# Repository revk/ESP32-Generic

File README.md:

# ESP32-Generic

Now at [Codeberg](https://codeberg.org/RevK/ESP32-Generic)

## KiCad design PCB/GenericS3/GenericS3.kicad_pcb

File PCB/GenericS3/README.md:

# GenericS3

## Trademark

This is an open source project, but bear in mind you cannot sell boards bearing the Andrews & Arnold Ltd name, the A&A logo, the registered trademark AJK logo, or the GS1 allocated EANs assigned to Andrews & Arnold Ltd.

## PCB Designs

These files are for use with [KiCAD](https://www.kicad.org).

- [GenericS3](GenericS3.kicad_pro)
## 3D

3D case designs are normally automatically created from the PCB so as to ensure correct details and placement of apertures, etc.

|Design|Bottom|Top|
|------|------|---|
|GenericS3|[GenericS3B](GenericS3B.stl)|[GenericS3T](GenericS3T.stl)|

## Images

---

*Auto generated README.md 2025-08-25T15:22:12*

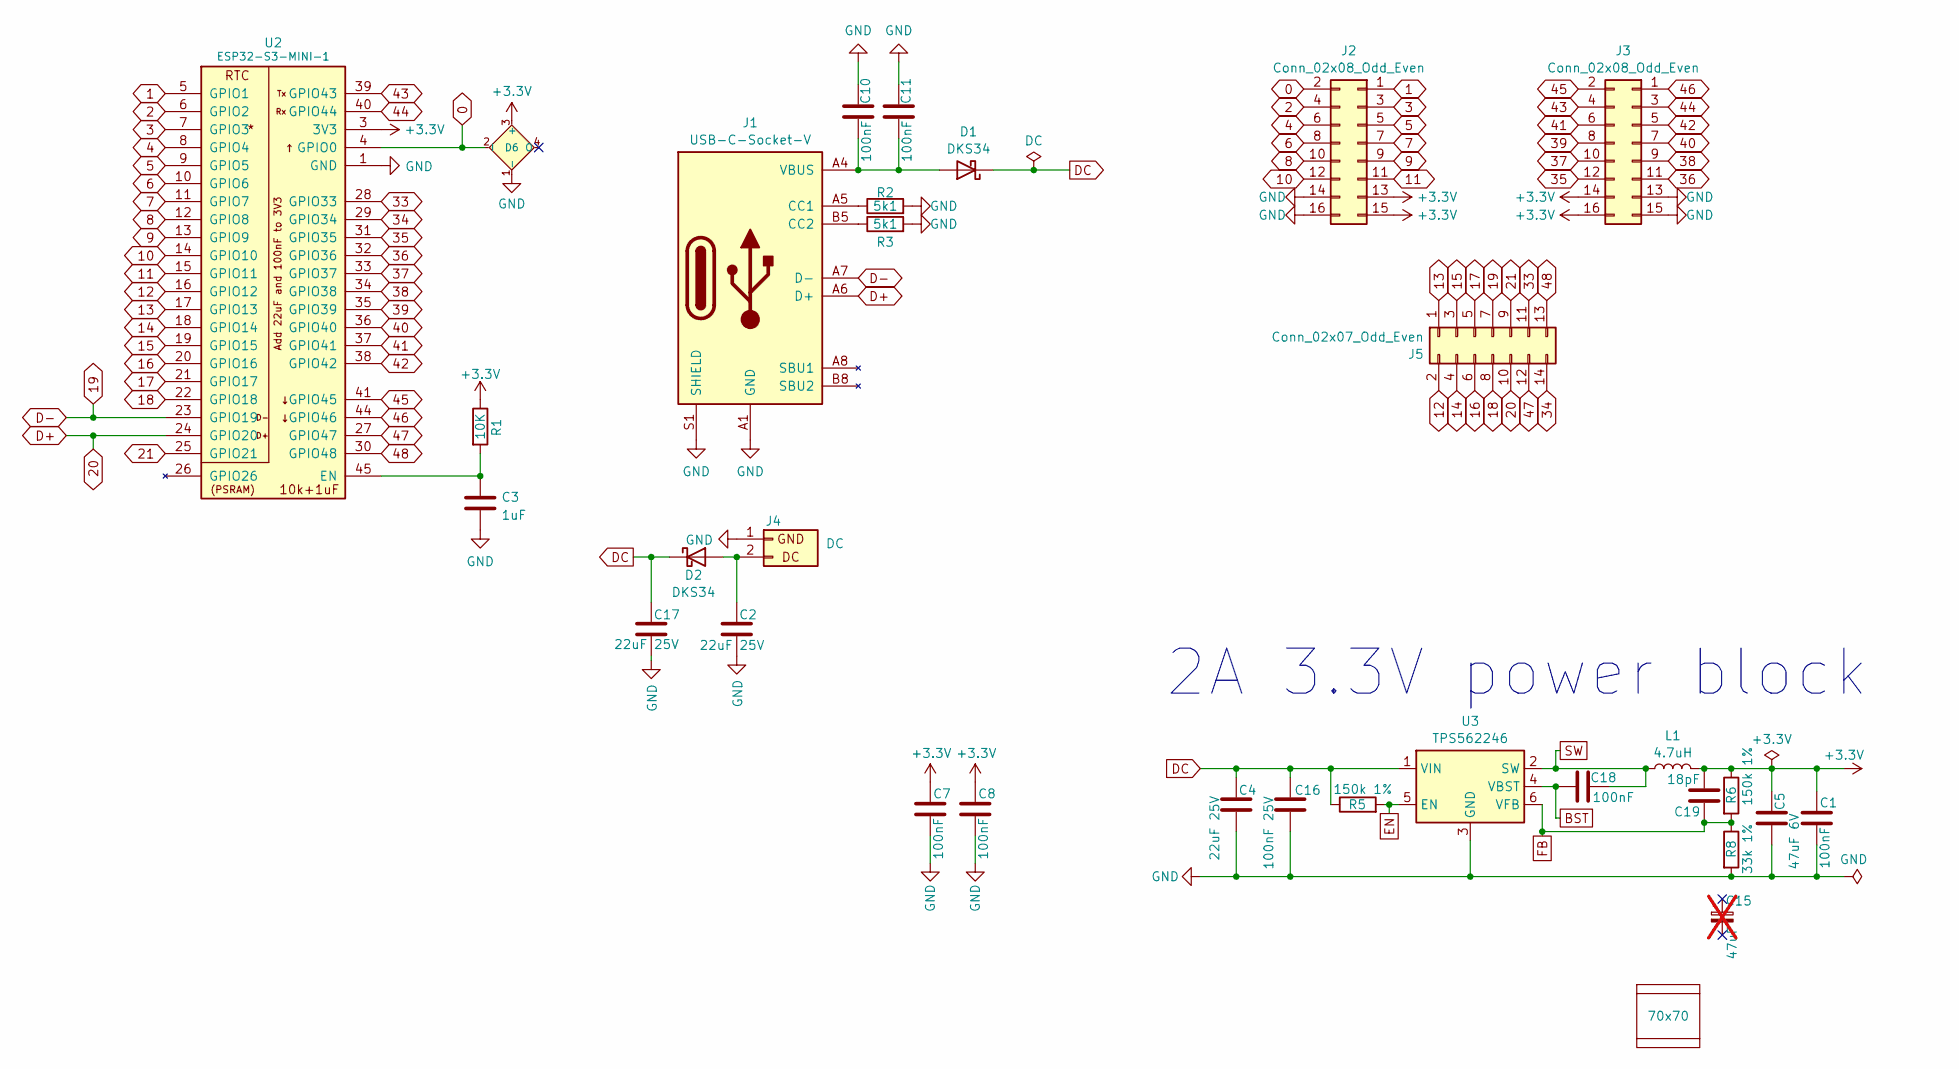
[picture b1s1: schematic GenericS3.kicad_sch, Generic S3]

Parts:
C1, C7, C8, C10, C11, C18: 100nF; C_0201; MPN C76934
C2, C4, C17: 22uF 25V; C_0805; MPN C45783
C3: 1uF; C_0201
C5: 47uF 6V; C_0805; MPN C16780
C15: 47uF; C_0805_Tant; MPN C1954938; not fitted
C16: 100nF 25V; C_0402; MPN C56392
C19: 18pF; C_0201; MPN C62164
D1, D2: DKS34; D_SOD-123FL; MPN C727076
D6: XL-1010RGBC-WS2812B; SMD1615; MPN C5349954
J1: USB-C-Socket-V; USB-C-Socket-H; MPN C709357
J2, J3: Conn_02x08_Odd_Even; PinHeader_2x08_P2.54mm_Vertical
J4: DC; WAGO-2060-452-998-404; MPN C2765055
J5: Conn_02x07_Odd_Even; PinHeader_2x07_P2.54mm_Vertical
L1: 4.7uH; L_5x5; MPN C307876
PCB1: 70x70; PCB7070
R1: 10K; R_0201; MPN C106225
R2, R3: 5k1; R_0201; MPN C274341
R5, R6: 150k 1%; R_0201; MPN C310173
R8: 33k 1%; R_0201; MPN C320835
U2: ESP32-S3-MINI-1; MPN C3013941
U3: TPS562246; SOT-563; MPN C41833479
V1, V2: 70; VCUT70

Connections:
0: D6.2 (I), J2.2, U2.4 (GPIO0)
1: J2.1, U2.5 (GPIO1)
2: J2.4, U2.6 (GPIO2)
3: J2.3, U2.7 (GPIO3)
4: J2.6, U2.8 (GPIO4)
5: J2.5, U2.9 (GPIO5)
6: J2.8, U2.10 (GPIO6)
7: J2.7, U2.11 (GPIO7)
8: J2.10, U2.12 (GPIO8)
9: J2.9, U2.13 (GPIO9)
10: J2.12, U2.14 (GPIO10)
11: J2.11, U2.15 (GPIO11)
12: J5.2, U2.16 (GPIO12)
13: J5.1, U2.17 (GPIO13)
14: J5.4, U2.18 (GPIO14)
15: J5.3, U2.19 (GPIO15)
16: J5.6, U2.20 (GPIO16)
17: J5.5, U2.21 (GPIO17)
18: J5.8, U2.22 (GPIO18)
19: J1.A7 (D-), J1.B7 (D-), J5.7, U2.23 (GPIO19)
20: J1.A6 (D+), J1.B6 (D+), J5.10, U2.24 (GPIO20)
21: J5.9, U2.25 (GPIO21)
33: J5.11, U2.28 (GPIO33)
34: J5.14, U2.29 (GPIO34)
35: J3.12, U2.31 (GPIO35)
36: J3.11, U2.32 (GPIO36)
37: J3.10, U2.33 (GPIO37)
38: J3.9, U2.34 (GPIO38)
39: J3.8, U2.35 (GPIO39)
40: J3.7, U2.36 (GPIO40)
41: J3.6, U2.37 (GPIO41)
42: J3.5, U2.38 (GPIO42)
43: J3.4, U2.39 (GPIO43)
44: J3.3, U2.40 (GPIO44)
45: J3.2, U2.41 (GPIO45)
46: J3.1, U2.44 (GPIO46)
47: J5.12, U2.27 (GPIO47)
48: J5.13, U2.30 (GPIO48)
+3.3V: C1.2, C5.1, C7.2, C8.2, C19.2, D6.3 (+), J2.13, J2.15, J3.14, J3.16, L1.2, R1.1, R6.1, U2.3 (3V3)
BST: C18.1, U3.4 (VBST)
DC: C4.1, C16.1, C17.1, D1.1 (K), D2.1 (K), R5.1, U3.1 (VIN)
EN: R5.2, U3.5 (EN)
FB: C19.1, R6.2, R8.1, U3.6 (VFB)
GND: C1.1, C2.2, C3.2, C4.2, C5.2, C7.1, C8.1, C10.2, C11.2, C16.2, C17.2, D6.1 (-), J1.A1 (GND), J1.A12 (GND), J1.B1 (GND), J1.B12 (GND), J1.S1 (SHIELD), J2.14, J2.16, J3.13, J3.15, J4.1 (GND), R2.2, R3.2, R8.2, U2.1 (GND), U2.2 (GND), U2.42 (GND), U2.43 (GND), U2.46 (GND), U2.47 (GND), U2.48 (GND), U2.49 (GND), U2.50 (GND), U2.51 (GND), U2.52 (GND), U2.53 (GND), U2.54 (GND), U2.55 (GND), U2.56 (GND), U2.57 (GND), U2.58 (GND), U2.59 (GND), U2.60 (GND), U2.61 (GND), U2.62 (GND), U2.63 (GND), U2.64 (GND), U2.65 (GND), U3.3 (GND)
unnamed: C10.1, C11.1, D1.2 (A), J1.A4 (VBUS), J1.A9 (VBUS), J1.B4 (VBUS), J1.B9 (VBUS)
unnamed: C2.1, D2.2 (A), J4.2 (DC)
unnamed: J1.A5 (CC1), R2.1
unnamed: J1.B5 (CC2), R3.1
unnamed: C3.1, R1.2, U2.45 (EN)
SW: C18.2, L1.1, U3.2 (SW)

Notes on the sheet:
2A 3.3V power block

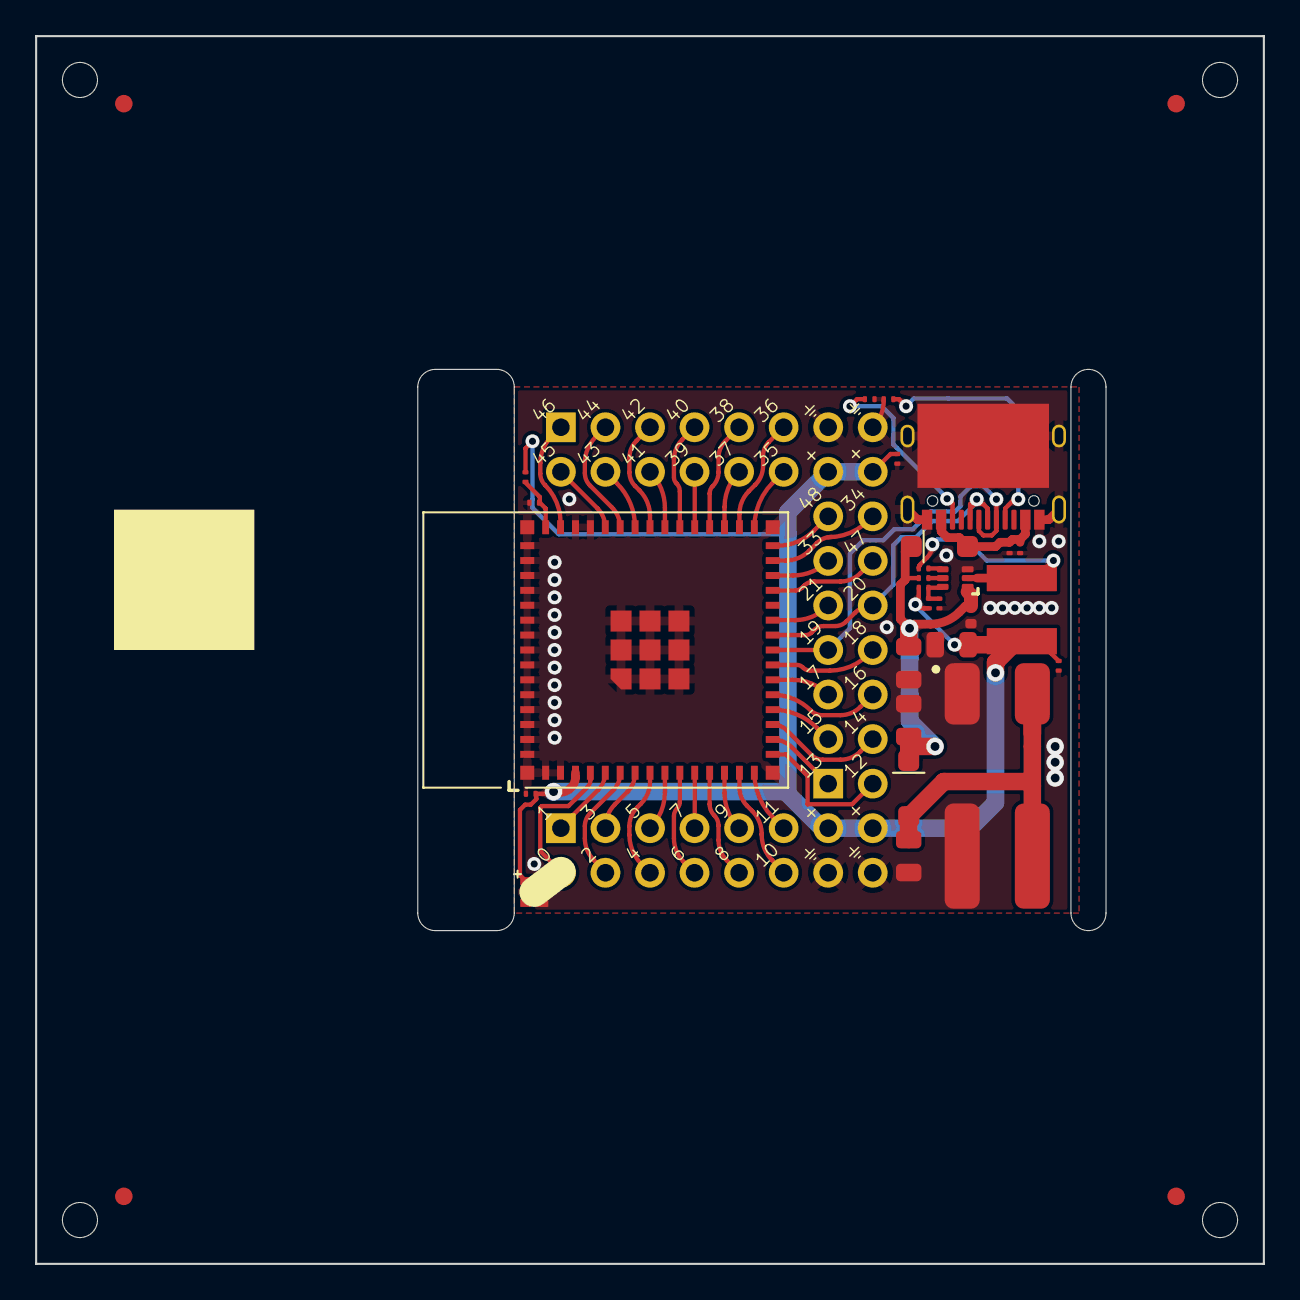
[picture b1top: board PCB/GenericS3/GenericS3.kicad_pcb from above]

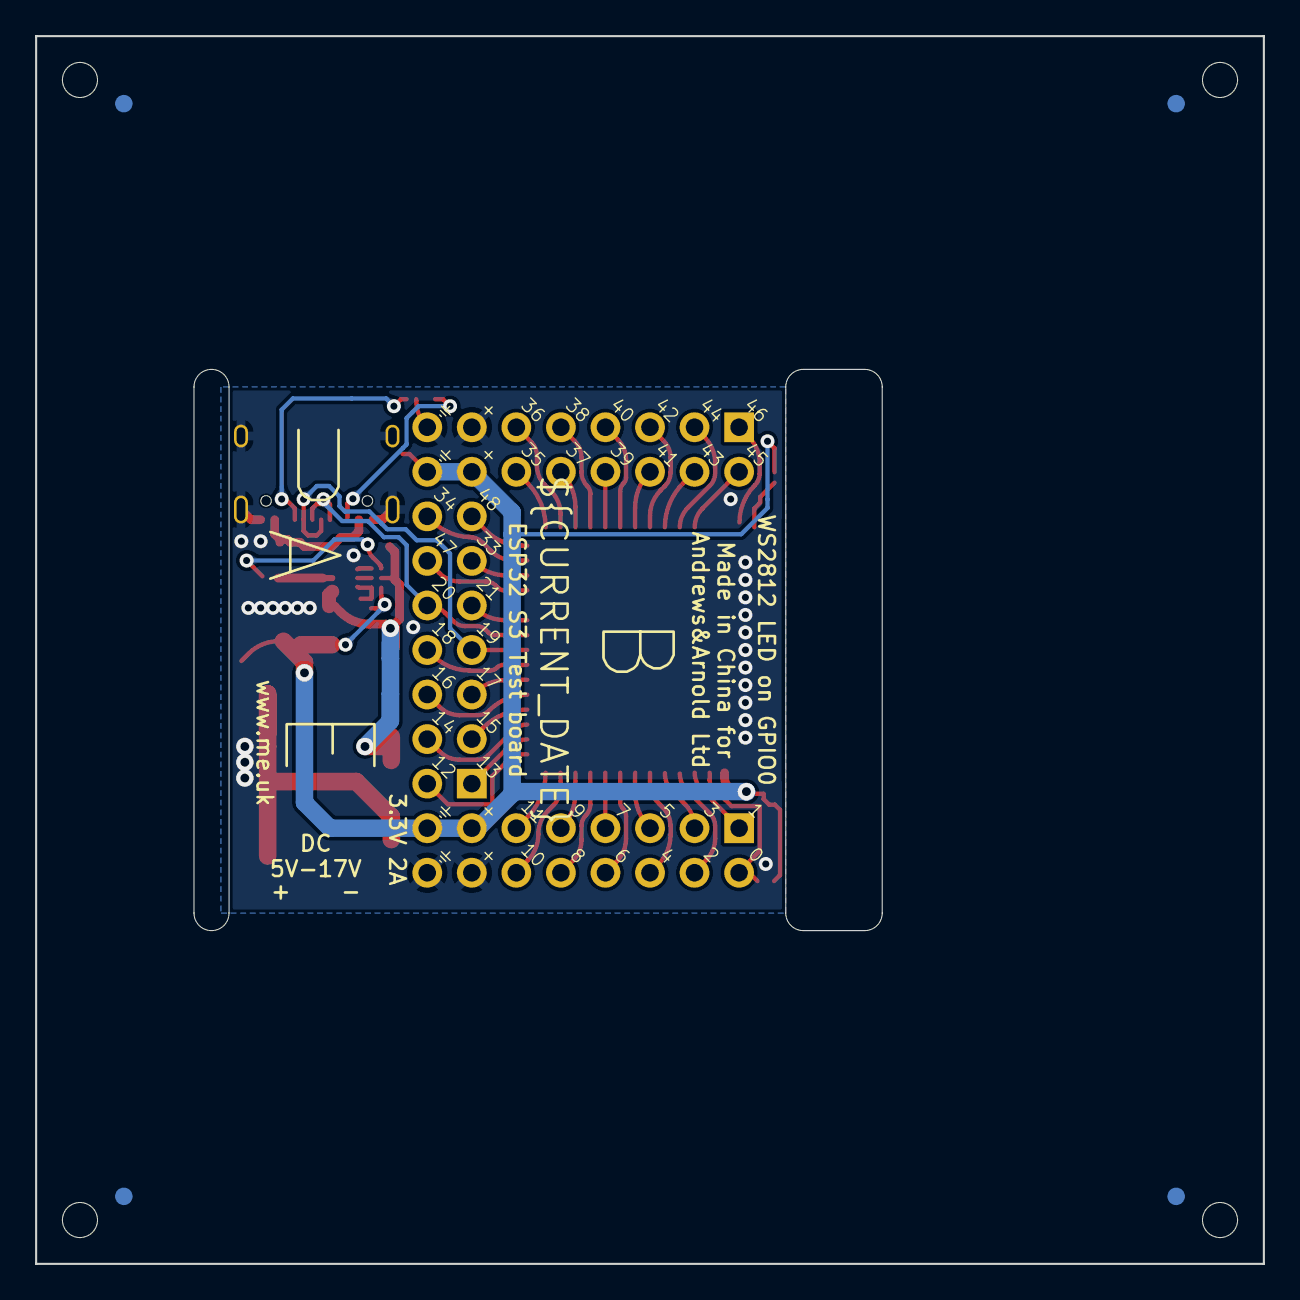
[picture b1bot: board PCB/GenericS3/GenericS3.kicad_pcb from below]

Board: 2 copper layers, 70.0 x 70.0 mm, 33 parts (5 on the bottom side), 50 nets.

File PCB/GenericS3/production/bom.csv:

Designator,Footprint,Quantity,Value,LCSC Part #
"C1, C10, C11, C18, C7, C8",C_0201,6,100nF,C76934
C16,C_0402,1,100nF 25V,C56392
"C17, C2, C4",C_0805,3,22uF 25V,C45783
C19,C_0201,1,18pF,C62164
C3,C_0201,1,1uF,
C5,C_0805,1,47uF 6V,C16780
"D1, D2",D_SOD-123FL,2,DKS34,C727076
D6,SMD1010-Side2,1,XL-1010RGBC-WS2812B,C5349953
J1,USB-C-Socket-H,1,USB-C-Socket-V,C709357
"J2, J3",PinHeader_2x08_P2.54mm_Vertical,2,Conn_02x08_Odd_Even,
J4,WAGO-2060-452-998-404,1,DC,C2765055
J5,PinHeader_2x07_P2.54mm_Vertical,1,Conn_02x07_Odd_Even,
L1,L_5x5,1,4.7uH,C307876
R1,R_0201,1,10K,C106225
"R2, R3",R_0201,2,5k1,C274341
"R5, R6",R_0201,2,150k 1%,C310173
R8,R_0201,1,33k 1%,C320835
U2,ESP32-S3-MINI-1,1,ESP32-S3-MINI-1,C3013941
U3,SOT-563,1,TPS562246,C41833479

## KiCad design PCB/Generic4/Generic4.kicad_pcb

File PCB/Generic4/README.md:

# Generic4

## Trademark

This is an open source project, but bear in mind you cannot sell boards bearing the Andrews & Arnold Ltd name, the A&A logo, the registered trademark AJK logo, or the GS1 allocated EANs assigned to Andrews & Arnold Ltd.

## PCB Designs

These files are for use with [KiCAD](https://www.kicad.org).

- [Generic4](Generic4.kicad_pro)
## 3D

3D case designs are normally automatically created from the PCB so as to ensure correct details and placement of apertures, etc.

- [Generic4](Generic4.stl)

## Images

---

*Auto generated README.md 2025-08-25T14:29:06*

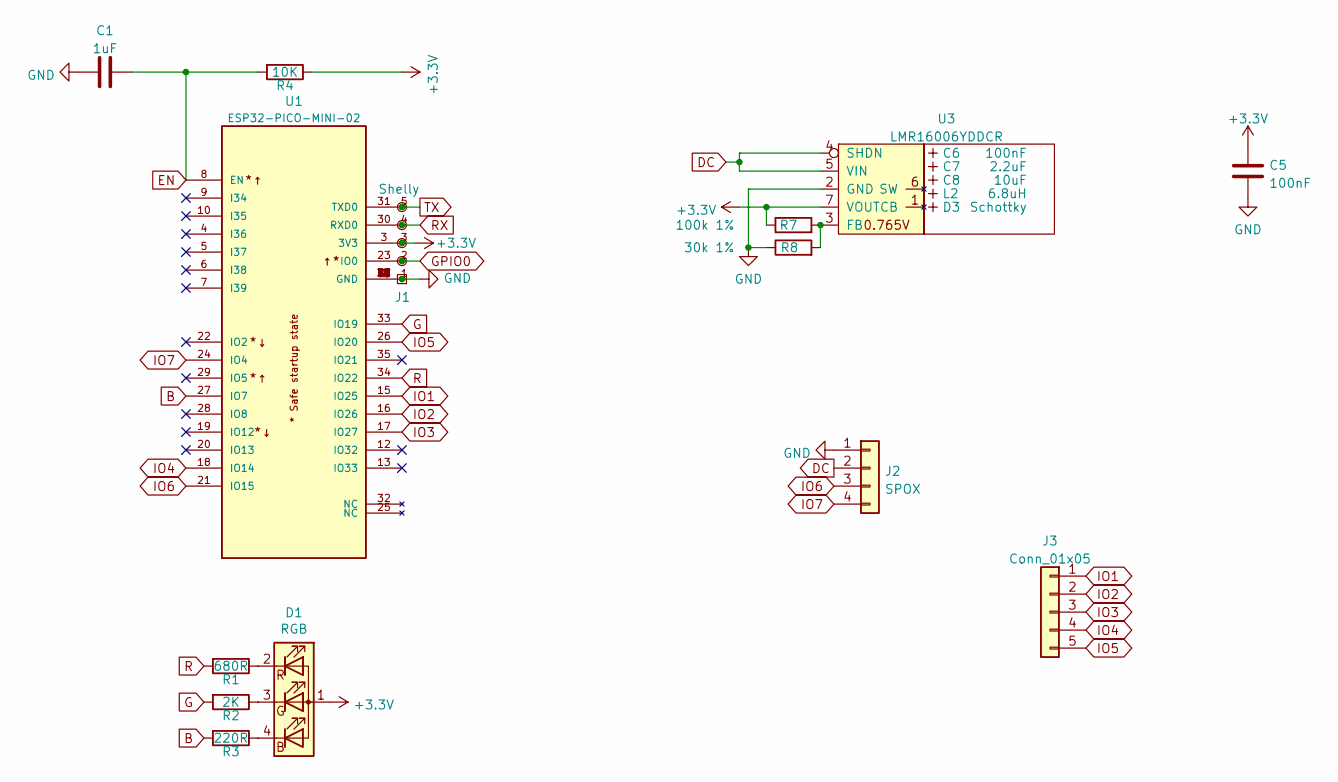
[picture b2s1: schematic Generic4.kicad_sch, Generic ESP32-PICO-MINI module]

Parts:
C1: 1uF; C_0603
C5: 100nF; C_0603
C6: 100nF; C_0603_; MPN C30926
C7: 2.2uF; C_0805_; MPN C19110
C8: 10uF; C_0805_; MPN C17024
D1: RGB; LED-RGB-1.6x1.6; Part No APTF1616LSEEZGKQBKC
D3: Schottky; D_1206_; MPN C143805
J1: Shelly
J2: SPOX; Molex_MiniSPOX_H4RA
J3: Conn_01x05; PinSocket_1x05_P2.54mm_Vertical
L2: 6.8uH; L_4x4_; MPN C354575
R1: 680R; R_0603
R2: 2K; R_0603
R3: 220R; R_0603
R4: 10K; R_0603
R7: 100k 1%; R_0603; MPN C14675
R8: 30k 1%; R_0603; MPN C100001
U1: ESP32-PICO-MINI-02; PARTREV v1.0
U3: LMR16006YDDCR; SOT-23-Thin-6-Reg; Part No LMR16006YDDCR

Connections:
+3.3V: C5.1, D1.1 (A), J1.3 (3V3), R4.1, R7.1, U1.3 (3V3), U3.7 (VOUT)
B: R3.2, U1.27 (IO7)
DC: J2.2, U3.4 (SHDN), U3.5 (VIN)
EN: C1.2, R4.2, U1.8 (EN)
G: R2.2, U1.33 (IO19)
GND: C1.1, C5.2, J1.1 (GND), J2.1, R8.1, U1.1 (GND), U1.2 (GND), U1.11 (GND), U1.14 (GND), U1.36 (GND), U1.37 (GND), U1.38 (GND), U1.39 (GND), U1.40 (GND), U1.41 (GND), U1.42 (GND), U1.43 (GND), U1.44 (GND), U1.45 (GND), U1.46 (GND), U1.47 (GND), U1.48 (GND), U1.49 (GND), U1.50 (GND), U1.51 (GND), U1.52 (GND), U1.53 (GND), U3.2 (GND)
GPIO0: J1.2 (0), U1.23 (IO0)
IO1: J3.1, U1.15 (IO25)
IO2: J3.2, U1.16 (IO26)
IO3: J3.3, U1.17 (IO27)
IO4: J3.4, U1.18 (IO14)
IO5: J3.5, U1.26 (IO20)
IO6: J2.3, U1.21 (IO15)
IO7: J2.4, U1.24 (IO4)
unnamed: D1.4 (BK), R3.1
unnamed: D1.3 (GK), R2.1
unnamed: D1.2 (RK), R1.1
unnamed: R7.2, R8.2, U3.3 (FB)
R: R1.2, U1.34 (IO22)
RX: J1.4 (Rx), U1.30 (RXD0)
TX: J1.5 (Tx), U1.31 (TXD0)

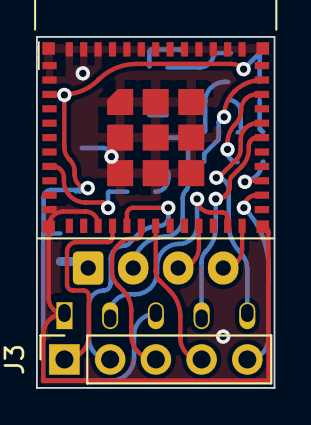
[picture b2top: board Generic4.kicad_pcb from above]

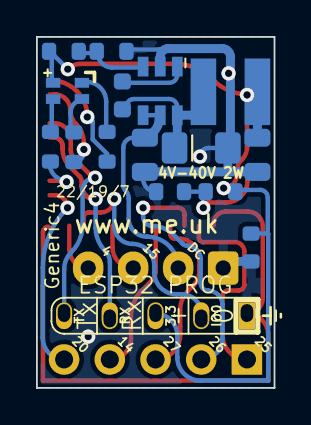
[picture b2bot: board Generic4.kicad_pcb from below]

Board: 2 copper layers, 13.2 x 19.5 mm, 19 parts (16 on the bottom side), 21 nets.

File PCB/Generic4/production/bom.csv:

Designator,Footprint,Quantity,Value,LCSC Part #
C1,C_0603,1,1uF,
C5,C_0603,1,100nF,
C6,C_0603_,1,100nF,C30926
C7,C_0805_,1,2.2uF,C19110
C8,C_0805_,1,10uF,C17024
D1,LED-RGB-1.6x1.6,1,RGB,
D3,D_1206_,1,Schottky,C143805
J2,Molex_MiniSPOX_H4RA,1,SPOX,
J3,PinSocket_1x05_P2.54mm_Vertical,1,Conn_01x05,
L2,L_4x4_,1,6.8uH,C354575
R1,R_0603,1,680R,
R2,R_0603,1,2K,
R3,R_0603,1,220R,
R4,R_0603,1,10K,
R7,R_0603,1,100k 1%,C14675
R8,R_0603,1,30k 1%,C100001
U1,ESP32-PICO-MINI-02,1,ESP32-PICO-MINI-02,
U3,SOT-23-Thin-6-Reg,1,LMR16006YDDCR,C290195

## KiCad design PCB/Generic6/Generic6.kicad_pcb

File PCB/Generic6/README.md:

# Generic6

These files are for use in [KiCad](https://www.kicad.org).

## Trademark

This is an open source project, but bear in mind you cannot sell boards bearing the Andrews & Arnold Ltd name, the A&A logo, the registered trademark AJK logo, or the GS1 allocated EANs assigned to Andrews & Arnold Ltd.

## Images

*Auto generated 2025-08-24T13:35:26*

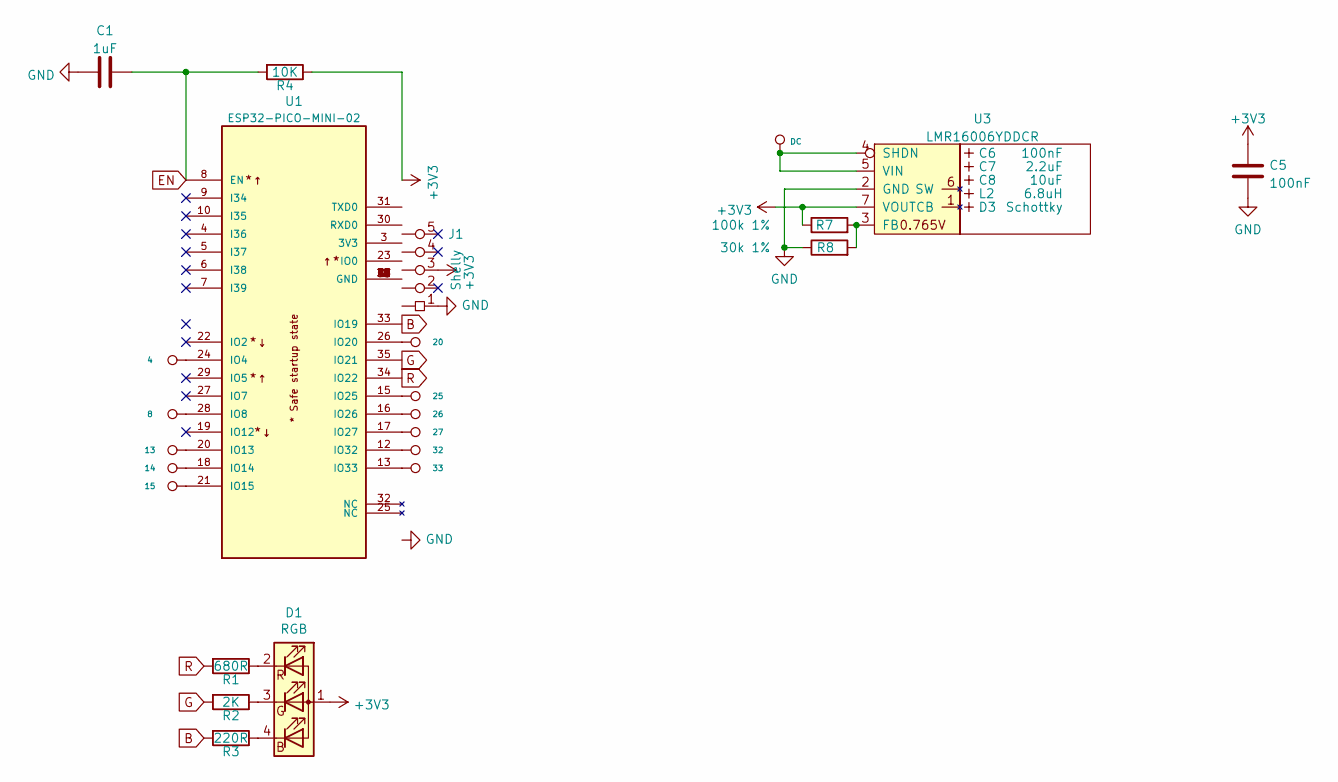
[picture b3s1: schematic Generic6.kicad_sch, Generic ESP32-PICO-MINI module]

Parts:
C1: 1uF; C_0402
C5: 100nF; C_0402
C6: 100nF; C_0603_; MPN C30926
C7: 2.2uF; C_0805_; MPN C19110
C8: 10uF; C_0805_; MPN C17024
D1: RGB; LED-RGB-1.6x1.6; Part No APTF1616LSEEZGKQBKC
D3: Schottky; D_1206_; MPN C143805
J1: Shelly
L2: 6.8uH; L_4x4_; MPN C354575
P1: 4; Round
P2: 32; Round
P3: 13; Round
P4: 25; Round
P5: 26; Round
P6: 33; Round
P7: 8; Round
P8: 27; Round
P9: 14; Round
P10: 20; Round
P11: 15; Round
P12: DC; Round
R1: 680R; R_0402
R2: 2K; R_0402
R3: 220R; R_0402
R4: 10K; R_0402
R7: 100k 1%; R_0603; MPN C14675
R8: 30k 1%; R_0603; MPN C100001
U1: ESP32-PICO-MINI-02; PARTREV v1.0
U3: LMR16006YDDCR; SOT-23-Thin-6-Reg; Part No LMR16006YDDCR

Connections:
+3V3: C5.1, D1.1 (A), J1.3 (3V3), R4.1, R7.1, U3.7 (VOUT)
B: R3.2, U1.33 (IO19)
EN: C1.2, R4.2, U1.8 (EN)
G: R2.2, U1.35 (IO21)
GND: C1.1, C5.2, J1.1 (GND), R8.1, U3.2 (GND)
unnamed: D1.4 (BK), R3.1
unnamed: D1.3 (GK), R2.1
unnamed: D1.2 (RK), R1.1
unnamed: P1.1, U1.24 (IO4)
unnamed: P2.1, U1.12 (IO32)
unnamed: P3.1, U1.20 (IO13)
unnamed: P4.1, U1.15 (IO25)
unnamed: P5.1, U1.16 (IO26)
unnamed: P6.1, U1.13 (IO33)
unnamed: P7.1, U1.28 (IO8)
unnamed: P8.1, U1.17 (IO27)
unnamed: P9.1, U1.18 (IO14)
unnamed: P10.1, U1.26 (IO20)
unnamed: P11.1, U1.21 (IO15)
unnamed: P12.1, U3.4 (SHDN), U3.5 (VIN)
unnamed: U1.1 (GND), U1.2 (GND), U1.11 (GND), U1.14 (GND), U1.36 (GND), U1.37 (GND), U1.38 (GND), U1.39 (GND), U1.40 (GND), U1.41 (GND), U1.42 (GND), U1.43 (GND), U1.44 (GND), U1.45 (GND), U1.46 (GND), U1.47 (GND), U1.48 (GND), U1.49 (GND), U1.50 (GND), U1.51 (GND), U1.52 (GND), U1.53 (GND)
unnamed: R7.2, R8.2, U3.3 (FB)
R: R1.2, U1.34 (IO22)

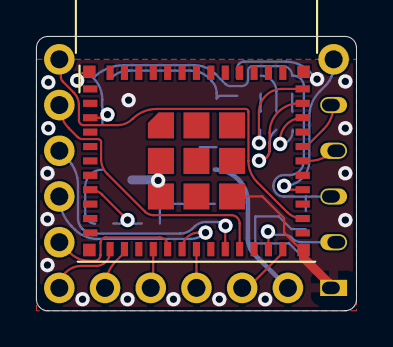
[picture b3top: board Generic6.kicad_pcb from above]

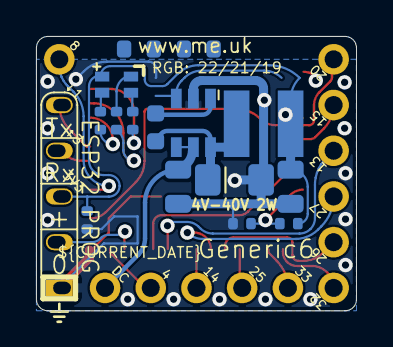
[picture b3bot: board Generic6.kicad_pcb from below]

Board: 2 copper layers, 17.8 x 15.2 mm, 29 parts (28 on the bottom side), 23 nets.

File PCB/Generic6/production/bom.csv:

Designator,Footprint,Quantity,Value,LCSC Part #
C1,C_0402,1,1uF,
C5,C_0402,1,100nF,
C6,C_0603_,1,100nF,C30926
C7,C_0805_,1,2.2uF,C19110
C8,C_0805_,1,10uF,C17024
D1,LED-RGB-1.6x1.6,1,RGB,
D3,D_1206_,1,Schottky,C143805
J1,Shelly,1,Shelly,
L2,L_4x4_,1,6.8uH,C354575
R1,R_0402,1,680R,
R2,R_0402,1,2K,
R3,R_0402,1,220R,
R4,R_0402,1,10K,
R7,R_0603,1,100k 1%,C14675
R8,R_0603,1,30k 1%,C100001
U1,ESP32-PICO-MINI-02,1,ESP32-PICO-MINI-02,
U3,SOT-23-Thin-6-Reg,1,LMR16006YDDCR,C290195

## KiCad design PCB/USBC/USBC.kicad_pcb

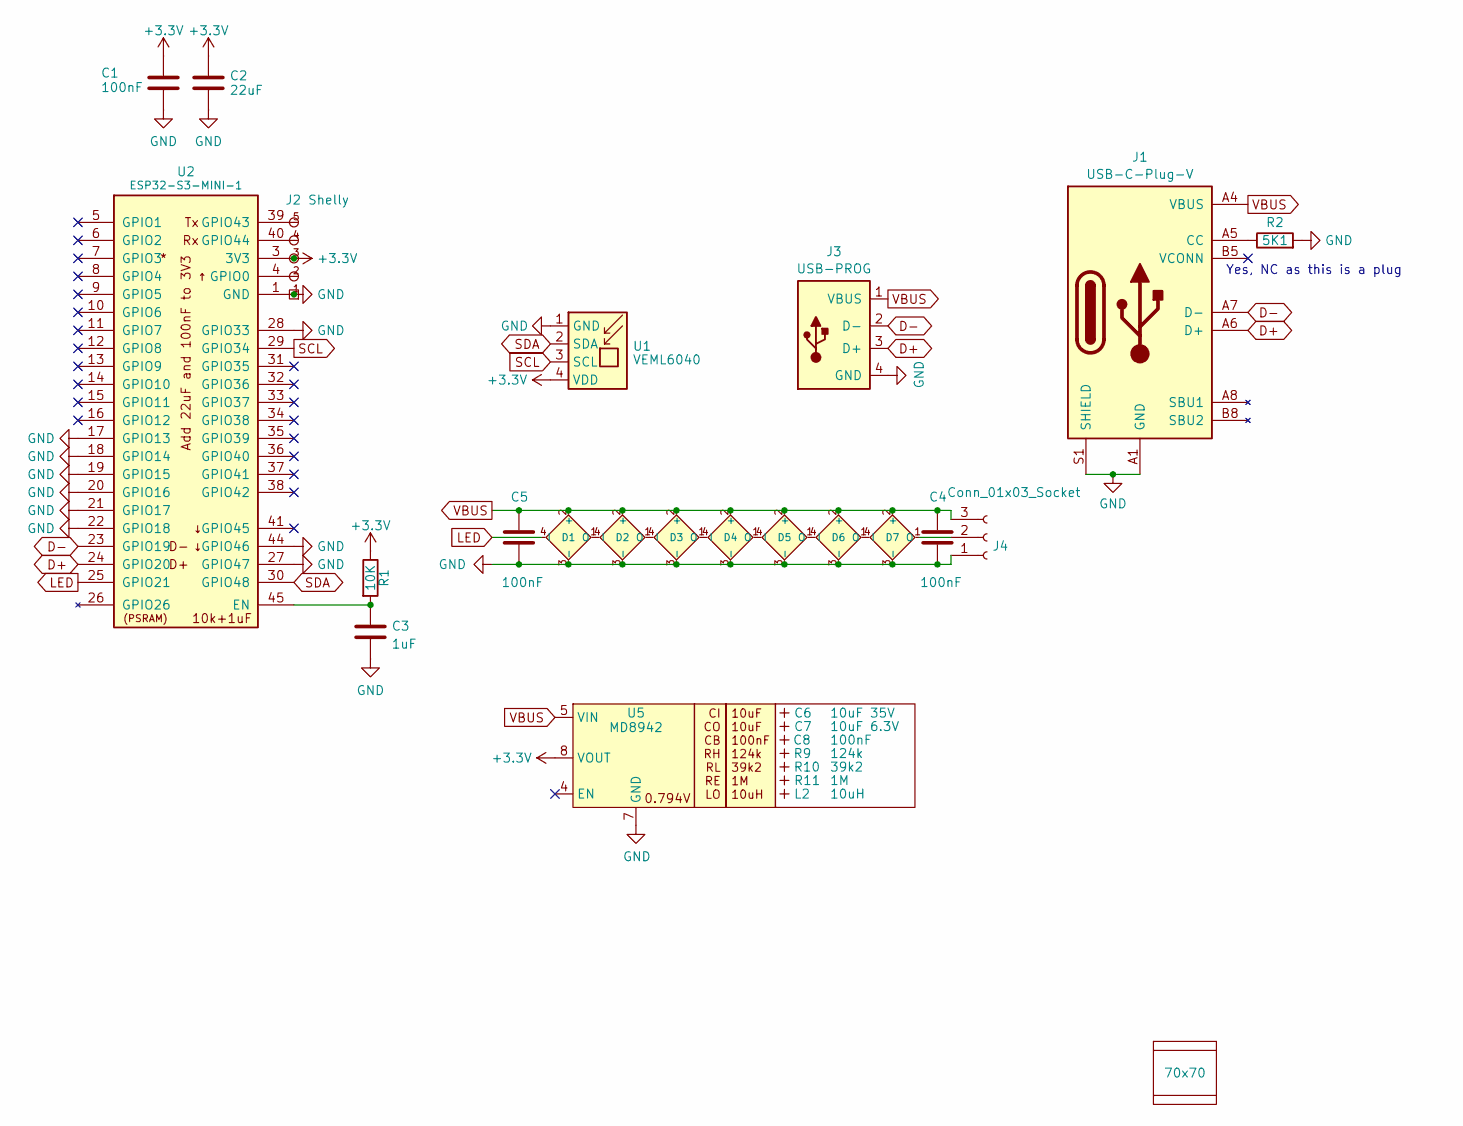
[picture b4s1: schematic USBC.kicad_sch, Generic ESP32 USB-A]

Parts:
C1, C4, C5: 100nF; C_0402
C2: 22uF; C_0402
C3: 1uF; C_0402
C6: 10uF 35V; C_0603_; MPN C194427
C7: 10uF 6.3V; C_0603_; MPN C1691
C8: 100nF; C_0603_
D1, D2, D3, D4, D5, D6, D7: XL-1010RGBC-WS2812B; SMD1010; MPN C5349953
J1: USB-C-Plug-V; MPN C399938
J2: Shelly
J3: USB-PROG
J4: Conn_01x03_Socket; PinHeader_1x03_P2.54mm
L2: 10uH; L_4x4_
PCB1: 70x70; PCB7070
R1: 10K; R_0402
R2: 5K1; R_0402
R9: 124k; R_0402_
R10: 39k2; R_0402_
R11: 1M; R_0402_
U1: VEML6040; MPN C78465
U2: ESP32-S3-MINI-1; MPN C3013941
U5: MD8942; SOT-23-6-MD8942; MPN C2684786
V1, V2: 70; VCUT70N

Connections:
+3.3V: C1.1, C2.1, J2.3 (3V3), R1.1, U1.4 (VDD), U2.3 (3V3), U5.8 (VOUT)
D+: J1.A6 (D+), J1.B6 (D+), J3.3 (D+), U2.24 (GPIO20)
D-: J1.A7 (D-), J1.B7 (D-), J3.2 (D-), U2.23 (GPIO19)
GND: C1.2, C2.2, C3.2, C4.2, C5.2, D1.3 (-), D2.3 (-), D3.3 (-), D4.3 (-), D5.3 (-), D6.3 (-), D7.3 (-), J1.A1 (GND), J1.A12 (GND), J1.B1 (GND), J1.B12 (GND), J1.S1 (SHIELD), J1.S2 (SHIELD), J2.1 (GND), J3.4 (GND), J4.1, R2.2, U1.1 (GND), U2.1 (GND), U2.2 (GND), U2.17 (GPIO13), U2.18 (GPIO14), U2.19 (GPIO15), U2.20 (GPIO16), U2.21 (GPIO17), U2.22 (GPIO18), U2.27 (GPIO47), U2.28 (GPIO33), U2.42 (GND), U2.43 (GND), U2.44 (GPIO46), U2.46 (GND), U2.47 (GND), U2.48 (GND), U2.49 (GND), U2.50 (GND), U2.51 (GND), U2.52 (GND), U2.53 (GND), U2.54 (GND), U2.55 (GND), U2.56 (GND), U2.57 (GND), U2.58 (GND), U2.59 (GND), U2.60 (GND), U2.61 (GND), U2.62 (GND), U2.63 (GND), U2.64 (GND), U2.65 (GND), U5.2 (GND), U5.7 (GND)
LED: D1.4 (I), U2.25 (GPIO21)
unnamed: D1.1 (O), D2.4 (I)
unnamed: D2.1 (O), D3.4 (I)
unnamed: D3.1 (O), D4.4 (I)
unnamed: D4.1 (O), D5.4 (I)
unnamed: D5.1 (O), D6.4 (I)
unnamed: D6.1 (O), D7.4 (I)
unnamed: D7.1 (O), J4.2
unnamed: J1.A5 (CC), R2.1
unnamed: J2.2 (0), U2.4 (GPIO0)
unnamed: J2.4 (Rx), U2.40 (GPIO44)
unnamed: J2.5 (Tx), U2.39 (GPIO43)
unnamed: C3.1, R1.2, U2.45 (EN)
SCL: U1.3 (SCL), U2.29 (GPIO34)
SDA: U1.2 (SDA), U2.30 (GPIO48)
VBUS: C4.1, C5.1, D1.2 (+), D2.2 (+), D3.2 (+), D4.2 (+), D5.2 (+), D6.2 (+), D7.2 (+), J1.A4 (VBUS), J1.A9 (VBUS), J1.B4 (VBUS), J1.B9 (VBUS), J3.1 (VBUS), J4.3, U5.5 (VIN)

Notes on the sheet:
Yes, NC as this is a plug

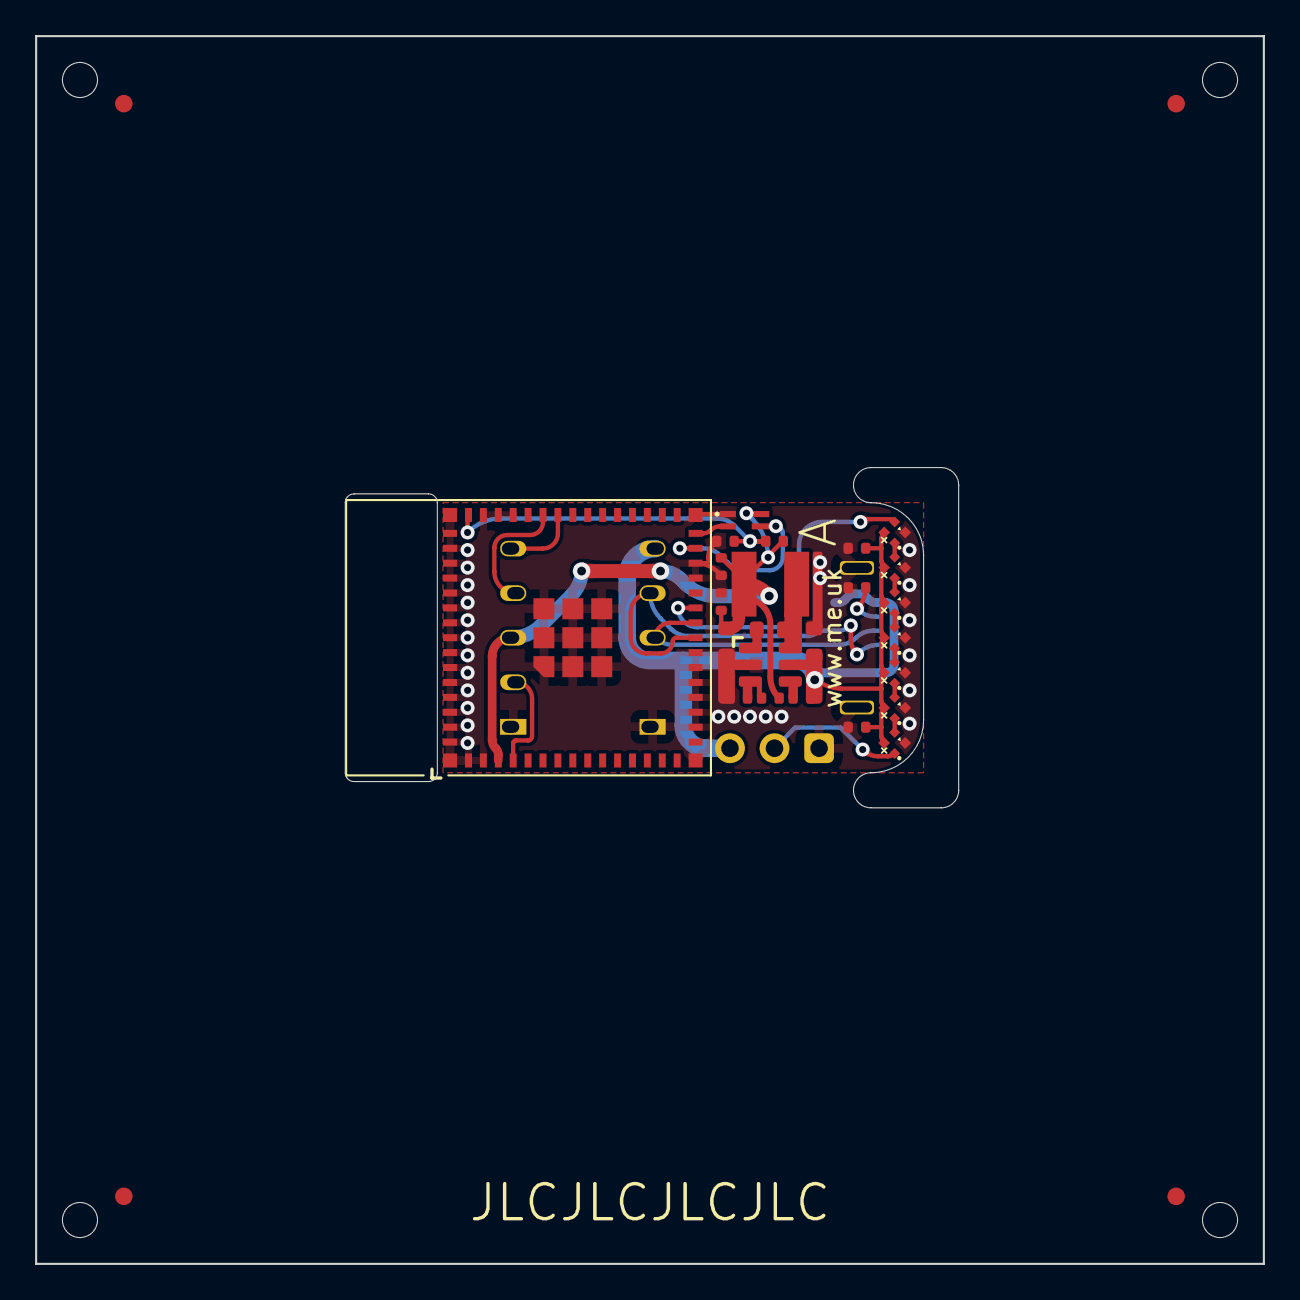
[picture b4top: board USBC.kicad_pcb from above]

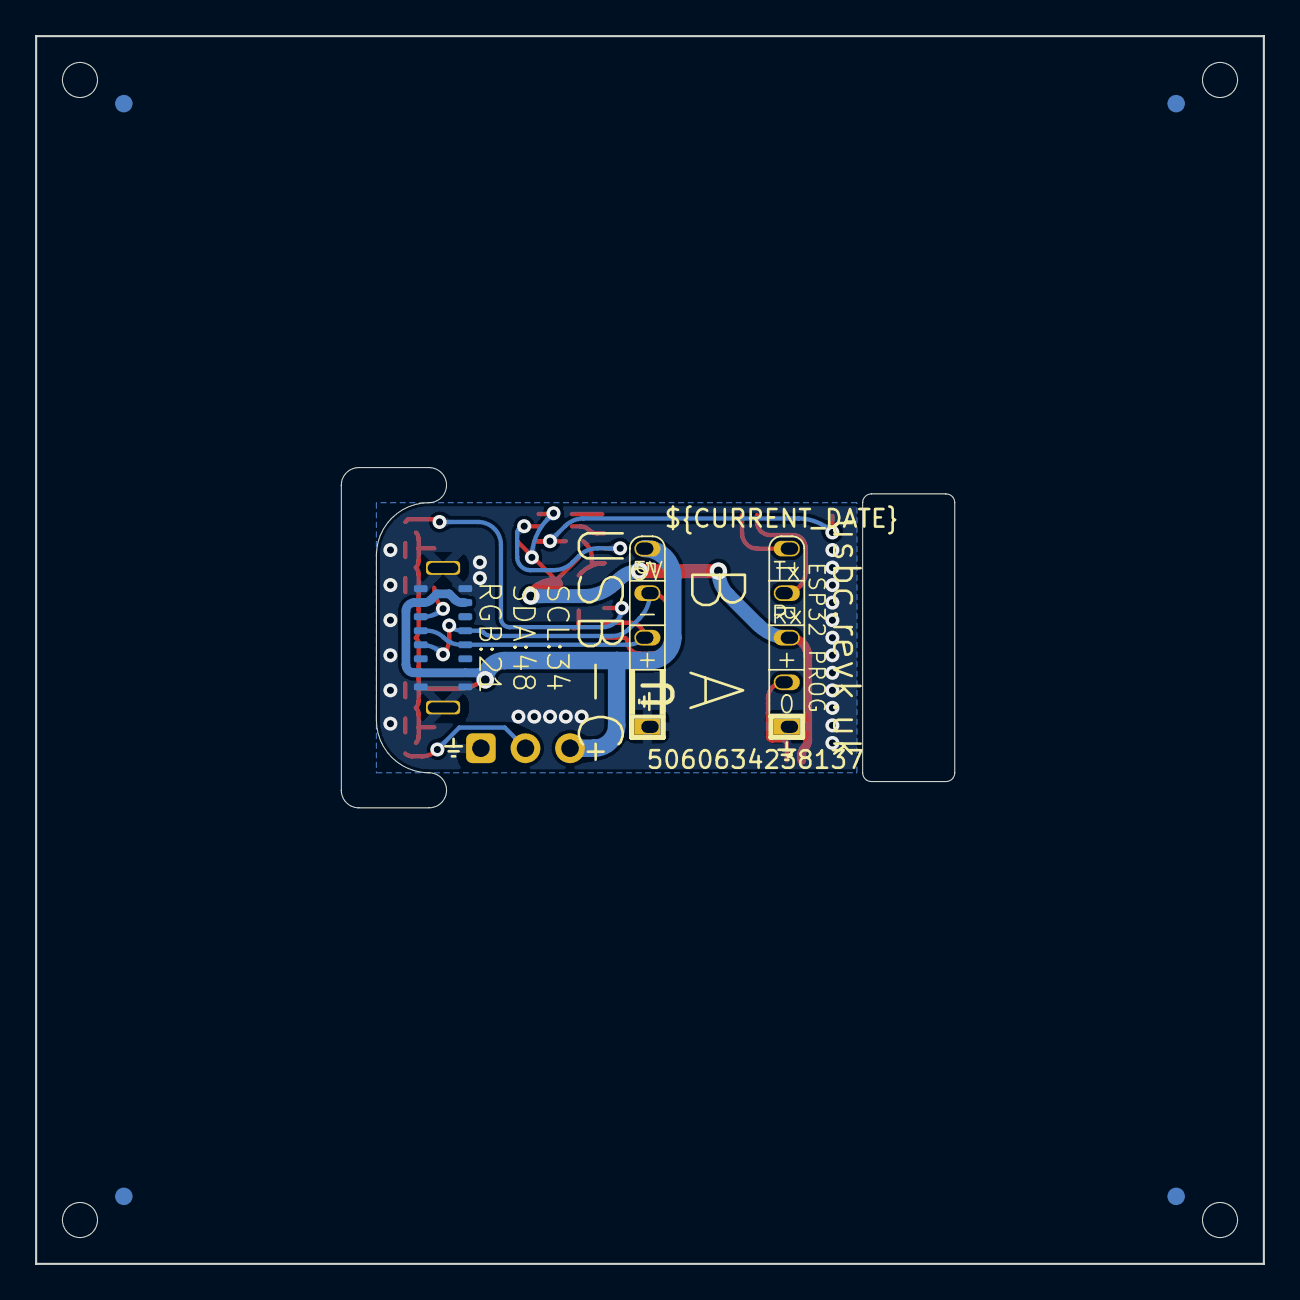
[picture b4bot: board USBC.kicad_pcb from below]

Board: 4 copper layers, 70.0 x 70.0 mm, 31 parts (5 on the bottom side), 20 nets.

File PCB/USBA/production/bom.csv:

Designator,Footprint,Quantity,Value,LCSC Part #
C1,C_0402,1,100nF,
C2,C_0402,1,22uF,
C3,C_0402,1,1uF,
C4,C_0603,1,10uF 35V,C194427
C6,C_0603_,1,10uF 35V,C194427
C7,C_0603_,1,10uF 6.3V,C1691
C8,C_0603_,1,100nF,
D1,SMD1010,1,XL-1010RGBC-WS2812B,C5349953
D2,DFN1006-2L,1,~,C5137770
J2,WAGO-2060-453-998-404,1,Conn_01x03,C2765056
L2,L_4x4_,1,10uH,
R1,R_0402,1,10K,
R10,R_0402_,1,39k2,
R11,R_0402_,1,1M,
R9,R_0402_,1,124k,
T1,T3902_MEMS_Mic,1,T3902_MEMS_Mic,C3171752
U1,VEML6040,1,VEML6040,C78465
U2,ESP32-S3-MINI-1,1,ESP32-S3-MINI-1,C3013941
U5,SOT-23-6-MD8942,1,MD8942,C2684786

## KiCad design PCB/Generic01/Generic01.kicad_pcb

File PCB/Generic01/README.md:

# Generic01

These files are for use in [KiCad](https://www.kicad.org).

## Trademark

This is an open source project, but bear in mind you cannot sell boards bearing the Andrews & Arnold Ltd name, the A&A logo, the registered trademark AJK logo, or the GS1 allocated EANs assigned to Andrews & Arnold Ltd.

## Images

*Auto generated 2025-08-24T13:28:44*

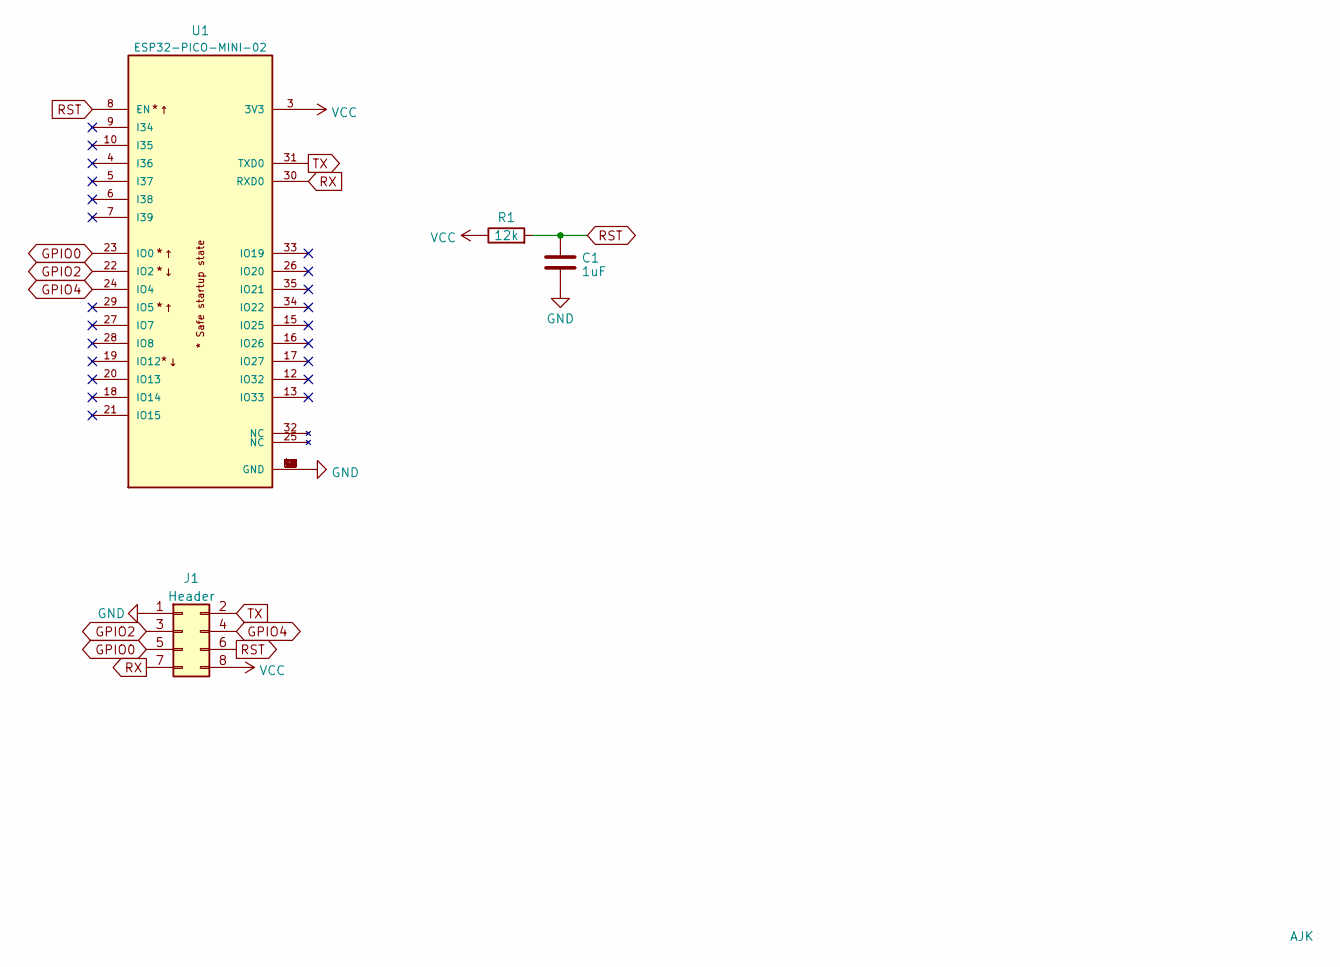
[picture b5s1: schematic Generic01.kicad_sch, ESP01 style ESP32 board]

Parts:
C1: 1uF; C_0603
J1: Header; PinHeader_2x04_P2.54mm_Vertical
Logo1: AJK
R1: 12k; R_0603
U1: ESP32-PICO-MINI-02; PARTREV v1.0

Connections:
GND: C1.2, J1.1, U1.1 (GND), U1.2 (GND), U1.11 (GND), U1.14 (GND), U1.36 (GND), U1.37 (GND), U1.38 (GND), U1.39 (GND), U1.40 (GND), U1.41 (GND), U1.42 (GND), U1.43 (GND), U1.44 (GND), U1.45 (GND), U1.46 (GND), U1.47 (GND), U1.48 (GND), U1.49 (GND), U1.50 (GND), U1.51 (GND), U1.52 (GND), U1.53 (GND)
GPIO0: J1.5, U1.23 (IO0)
GPIO2: J1.3, U1.22 (IO2)
GPIO4: J1.4, U1.24 (IO4)
RST: C1.1, J1.6, R1.2, U1.8 (EN)
RX: J1.7, U1.30 (RXD0)
TX: J1.2, U1.31 (TXD0)
VCC: J1.8, R1.1, U1.3 (3V3)

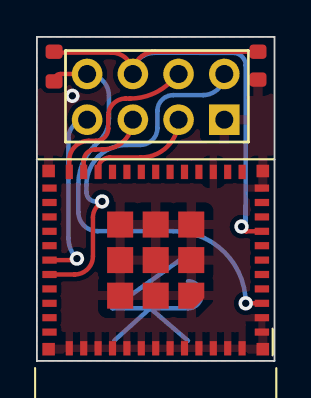
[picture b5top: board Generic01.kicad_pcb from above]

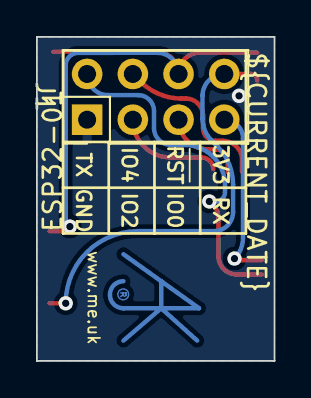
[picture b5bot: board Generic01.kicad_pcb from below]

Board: 2 copper layers, 13.2 x 18.0 mm, 5 parts (2 on the bottom side), 8 nets.

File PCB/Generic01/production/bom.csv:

Designator,Footprint,Quantity,Value,LCSC Part #
C1,C_0603,1,1uF,
J1,PinHeader_2x04_P2.54mm_Vertical,1,Header,v
R1,R_0603,1,12k,
U1,ESP32-PICO-MINI-02,1,ESP32-PICO-MINI-02,
